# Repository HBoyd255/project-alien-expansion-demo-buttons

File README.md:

# Project A.L.I.E.N. Expansion, Demo Buttons

<!-- Harry Boyd - 16/08/2024 - github.com/hboyd255 -->

The Project A.L.I.E.N. Main Board has been designed to to take expansion boards.
This utilises the 3 left-over GPIO pins, D11, D12 and D13.

This expansion board provides 3 buttons, each setting the robot to a different
demo mode.

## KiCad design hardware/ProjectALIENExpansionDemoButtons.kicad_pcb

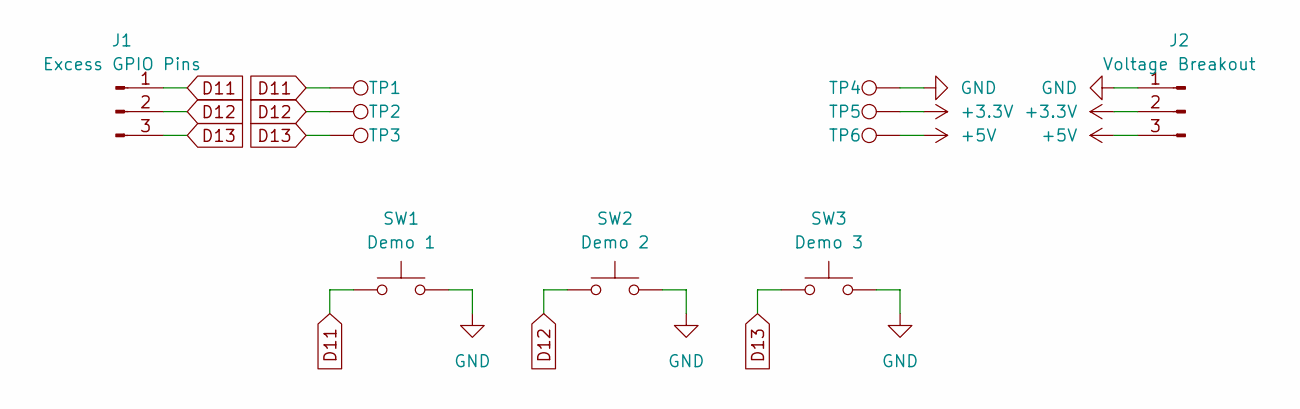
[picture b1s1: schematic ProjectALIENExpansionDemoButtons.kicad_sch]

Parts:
J1: Excess GPIO Pins; PinHeader_1x03_P2.54mm_Vertical
J2: Voltage Breakout; PinHeader_1x03_P2.54mm_Vertical
SW1: Demo 1; Two_Pin_Through_Hole_Push_Button
SW2: Demo 2; Two_Pin_Through_Hole_Push_Button
SW3: Demo 3; Two_Pin_Through_Hole_Push_Button
TP1, TP2, TP3, TP4, TP5, TP6: TestPoint; TestPoint_THTPad_D1.0mm_Drill0.5mm

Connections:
+3.3V: J2.2, TP5.1
+5V: J2.3, TP6.1
D11: J1.1, SW1.1, TP1.1
D12: J1.2, SW2.1, TP2.1
D13: J1.3, SW3.1, TP3.1
GND: J2.1, SW1.2, SW2.2, SW3.2, TP4.1

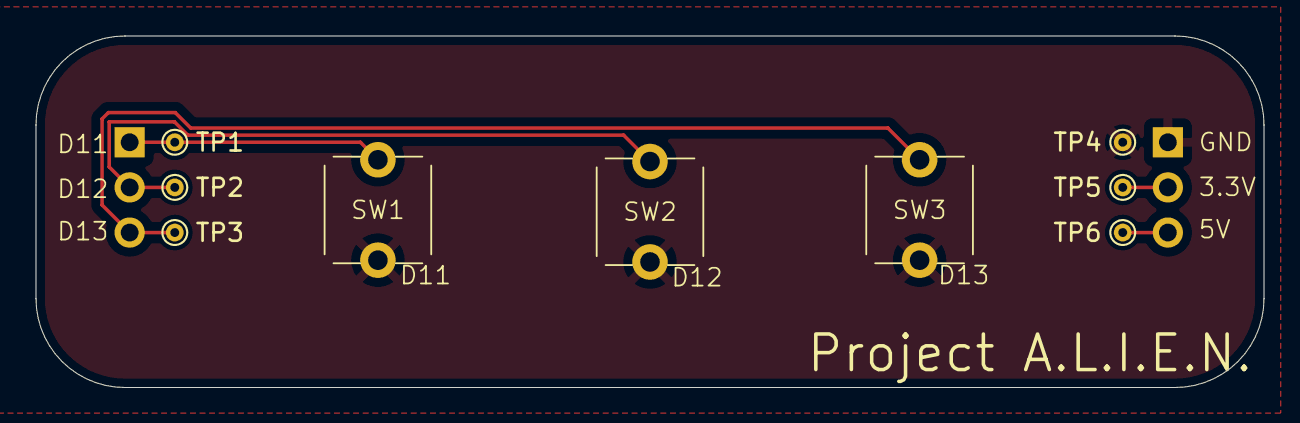
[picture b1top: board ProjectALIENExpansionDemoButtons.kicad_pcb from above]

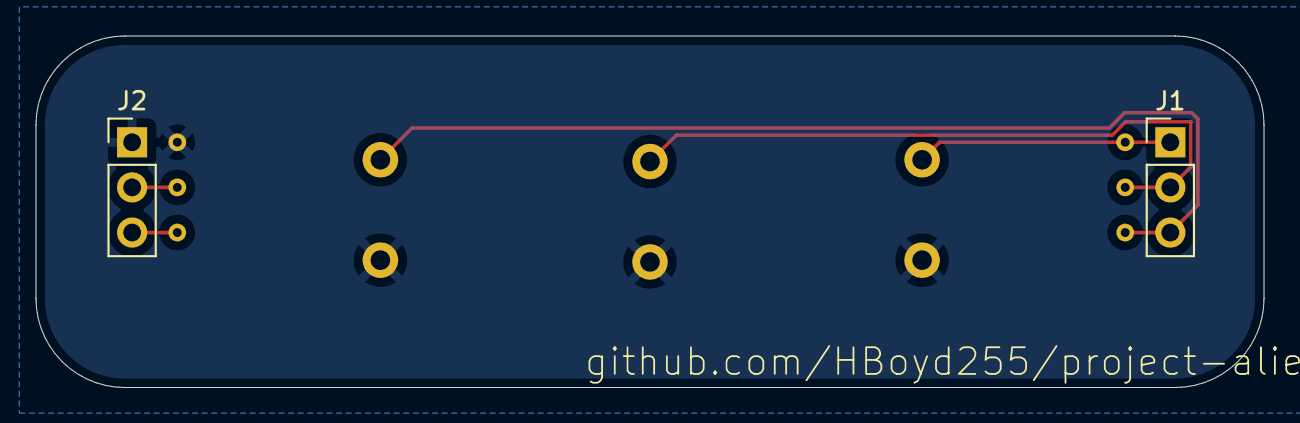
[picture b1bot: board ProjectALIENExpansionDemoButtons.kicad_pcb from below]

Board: 2 copper layers, 69.1 x 19.8 mm, 11 parts (2 on the bottom side), 6 nets.

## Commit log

2024-08-16 Created base expansion board
2024-08-16 Wired up buttons
2024-08-16 Added title to silkscreen
